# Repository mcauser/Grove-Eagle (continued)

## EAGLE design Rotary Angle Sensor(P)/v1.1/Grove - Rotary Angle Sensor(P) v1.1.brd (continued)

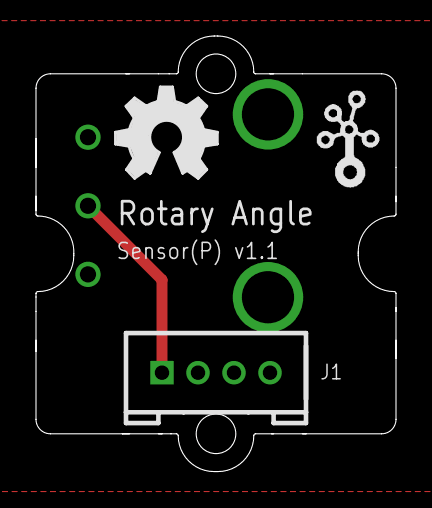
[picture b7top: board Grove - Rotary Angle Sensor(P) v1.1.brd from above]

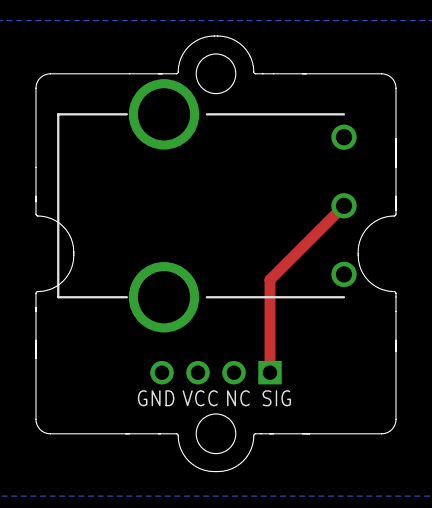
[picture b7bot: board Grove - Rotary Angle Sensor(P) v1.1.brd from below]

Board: 2 copper layers, 20.0 x 24.2 mm, 5 parts (2 on the bottom side), 3 nets.

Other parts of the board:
U$2: TWIGLOGO_SMALL
U$3: OSHW_FILLX200_NOTEXT
